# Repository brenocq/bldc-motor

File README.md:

<div align="center">
  
</div>

# BLDC Motor Controller

> [!NOTE]
> This project is currently in active development. Features and documentation are subject to change.

## Table of Contents
- [Project Overview](#project-overview)
- [Folder Structure](#folder-structure)
- [Mechanical](#mechanical)
- [Electronics](#electronics)
  - [MCU PCB (Top Board)](#mcu-pcb-top-board)
  - [Power PCB (Bottom Board)](#power-pcb-bottom-board)
- [Firmware](#firmware)
- [Simulation](#simulation)
- [Results](#results)
- [License](#license)

---

## Project Overview

This project aims to develop a **high-precision Brushless DC (BLDC) motor controller** from scratch, covering both hardware and firmware aspects. The controller is designed for advanced motor control applications, leveraging a powerful STM32 microcontroller, a dedicated motor driver IC, and comprehensive sensing capabilities for precise operation and rotor position estimation.

The core of the system is a custom two-board stack: an MCU board housing the main control logic and a power board managing motor drive and sensing.

## Folder Structure

The project is organized into logical directories to enhance maintainability and readability:

* `simulation/`: Contains code and files related to motor control simulation.
* `mechanical/`: Houses all mechanical design files (CAD models, part designs).
* `electronics/`: Stores KiCad project files for both the MCU and Power PCBs, including schematics and PCB layouts.
* `firmware/`: Contains all the embedded software for the STM32 microcontroller.
* `controller/`: Specific implementations of motor control algorithms (trapezoidal, FOC).
* `common/`: Shared utilities and communication definitions across different parts of the project.

---

## Mechanical

The mechanical aspects of this project are centered around integrating the custom electronics with an off-the-shelf **EM3215 BLDC motor**. It's important to note that, for this specific project, the **motor's original windings are being utilized**, and there are no plans to re-wrap the wire around the coils. The `mechanical` folder contains various CAD files (FreeCAD) for components like the rotor adapter, chassis, and PCB cutouts, ensuring a perfect fit and robust assembly.

<div align="center">
  
</div>

---

## Electronics

The electronics consist of two interconnected custom-designed Printed Circuit Boards (PCBs), designed using **KiCad**. Both boards are **4-layer designs** to facilitate efficient signal routing and power integrity. A **Molex PCB stack connector** is used to establish a robust electrical connection between the MCU and Power PCBs.

### MCU PCB (Top Board)

The top PCB serves as the brain of the controller, housing the main microcontroller and various sensors and interfaces for user interaction and precise feedback.

| Top Layer | Layer 1 | Layer 2 | Bottom Layer | 3D Top View | 3D Bottom View |
| :------------------: | :---------------: | :---------------: | :---------------------: | :---------: | :------------: |
|  |  |  |  |  |  |

**MCU PCB Key Components:**
- **STM32F4 Microcontroller:** The central processing unit for control algorithms, sensor data acquisition, and communication.
- **AS5048A Angle Position Encoder:** Provides 14-bit absolute rotor position feedback for precise commutation and control.
- **SK6805 LED Ring:** A customizable visual indicator for status and debugging.
- **Reset Button:** For convenient system resets.
- **ISM330DHCX IMU (Inertial Measurement Unit):** Provides acceleration and angular velocity data, useful for advanced motion control or system stabilization.

**MCU PCB v1.0 Release Package:**
- **[KiCad Project](https://github.com/brenocq/bldc-motor/tree/electronics/v1.0/electronics/BLDCM-MCU)**
- **[Schematic (PDF)](https://github.com/brenocq/bldc-motor/blob/electronics/v1.0/electronics/BLDCM-MCU/BLDCM-MCU.pdf)**
- **[Interactive BOM (HTML)](https://brenocq.s3.us-east-1.amazonaws.com/BLDCM/BLDCM-MCU-BOM-v1.0.html)**
- **[Gerbers (ZIP)](https://github.com/brenocq/bldc-motor/releases/download/electronics%2Fv1.0/BLDCM-MCU-v1.0-gerber.zip)**

### Power PCB (Bottom Board)

The bottom PCB handles the high-current motor driving functions and essential power monitoring.

| Top Layer | Layer 1 | Layer 2 | Bottom Layer | 3D Top View | 3D Bottom View |
| :------------------: | :---------------: | :---------------: | :---------------------: | :---------: | :------------: |
|  |  |  |  |  |  |

**Power PCB Key Components:**
- **TMC6300 Motor Driver:** A 3-phase motor driver that translates the MCU's PWM and control signals into high-current outputs for the motor phases.
- **TCAN1462 CAN Transceiver:** Enables robust CAN FD communication for daisy-chaining motors in series.
- **J-Link Connector:** Provides easy SWD debugging and programming for the STM32 microcontroller.
- **USB Connector:** Facilitates direct USB Full-Speed communication for data logging, control, and power input.
- **Micro-Lock Plus Connectors:** Robust 4-pin Molex connectors that provide a vibration-resistant link for power delivery and CAN bus communications.
- **Voltage Sensors (x4):** One monitors the DC bus voltage, while three dedicated sensors measure filtered phase voltages for safe operation and FOC.
- **INA240 Current Sensors (x3):** Three precision analog-output current sensors enable high-speed, accurate phase current measurement for FOC.

**Power PCB v1.0 Release Package:**
- **[KiCad Project](https://github.com/brenocq/bldc-motor/tree/electronics/v1.0/electronics/BLDCM-Power)**
- **[Schematic (PDF)](https://github.com/brenocq/bldc-motor/blob/electronics/v1.0/electronics/BLDCM-Power/BLDCM-Power.pdf)**
- **[Interactive BOM (HTML)](https://brenocq.s3.us-east-1.amazonaws.com/BLDCM/BLDCM-Power-BOM-v1.0.html)**
- **[Gerbers (ZIP)](https://github.com/brenocq/bldc-motor/releases/download/electronics%2Fv1.0/BLDCM-Power-v1.0-gerber.zip)**

---

## Firmware

The firmware, developed for the **STM32F4** microcontroller, is the intelligence behind the motor control. It includes:

* **Low-level Peripheral Drivers:** Custom drivers for ADC, timers, GPIO, SPI, I2C, UART, USB, and DMA to efficiently manage hardware resources.
* **Motor Control Algorithms:** Implementation of both **trapezoidal** and **Field-Oriented Control (FOC)** algorithms, located in the `controller` directory, to provide flexible and high-performance motor driving capabilities.
* **Sensor Integration:** Code to interface with the MT6701 encoder, INA239-Q1 current sensors, voltage sensor, and ISM330DHCX IMU for comprehensive feedback.
* **System Utilities:** Logging, error handling, and platform-specific configurations for the STM32 environment.

_The firmware architecture and design decisions will be documented in the future._

---

## Simulation

The `simulation` directory contains resources for simulating the BLDC motor system and visualizing the sensor data in real time. This allows for testing and validating control algorithms and system behavior in a virtual environment before deployment on the hardware. The `bldc.atta` file can be opened with [Atta](https://github.com/brenocq/atta), and it implements a basic motor model simulation and plotting of sensor data.

_Instructions on how to run the BLDCM simulation with [Atta](https://github.com/brenocq/atta) will be added in the future_

---

## Results

Below are some pictures/videos taken during the development. The controller design and calibration procedures will be explained in depth in the future :)

https://github.com/user-attachments/assets/e86b0316-7ecf-4e15-9d3b-c0315d690438

<div align="center">

</div>

## License
This project is licensed under the MIT License - check [LICENSE](LICENSE) for details.

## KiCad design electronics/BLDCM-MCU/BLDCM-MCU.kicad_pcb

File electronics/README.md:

# BLDCM Electronics
These KiCad projects were made with KiCad 9.0, make sure to use the same version or a newer one.

The schematic PDFs are available in `BLDCM-Power/BLDCM-Power.pdf` and `BLDCM-MCU/BLDCM-MCU.pdf`. The Gerber files and interactive BOM can be found in the release section of the repository.

> [!IMPORTANT]
> This project depends on the [BrenoCQ KiCad library](https://github.com/brenocq/brenocq-kicad-library), included as a Git submodule. To ensure all symbols, footprints, and 3D models are available, you must initialize the submodules:
>
> ```bash
> git submodule update --init --recursive
> ```

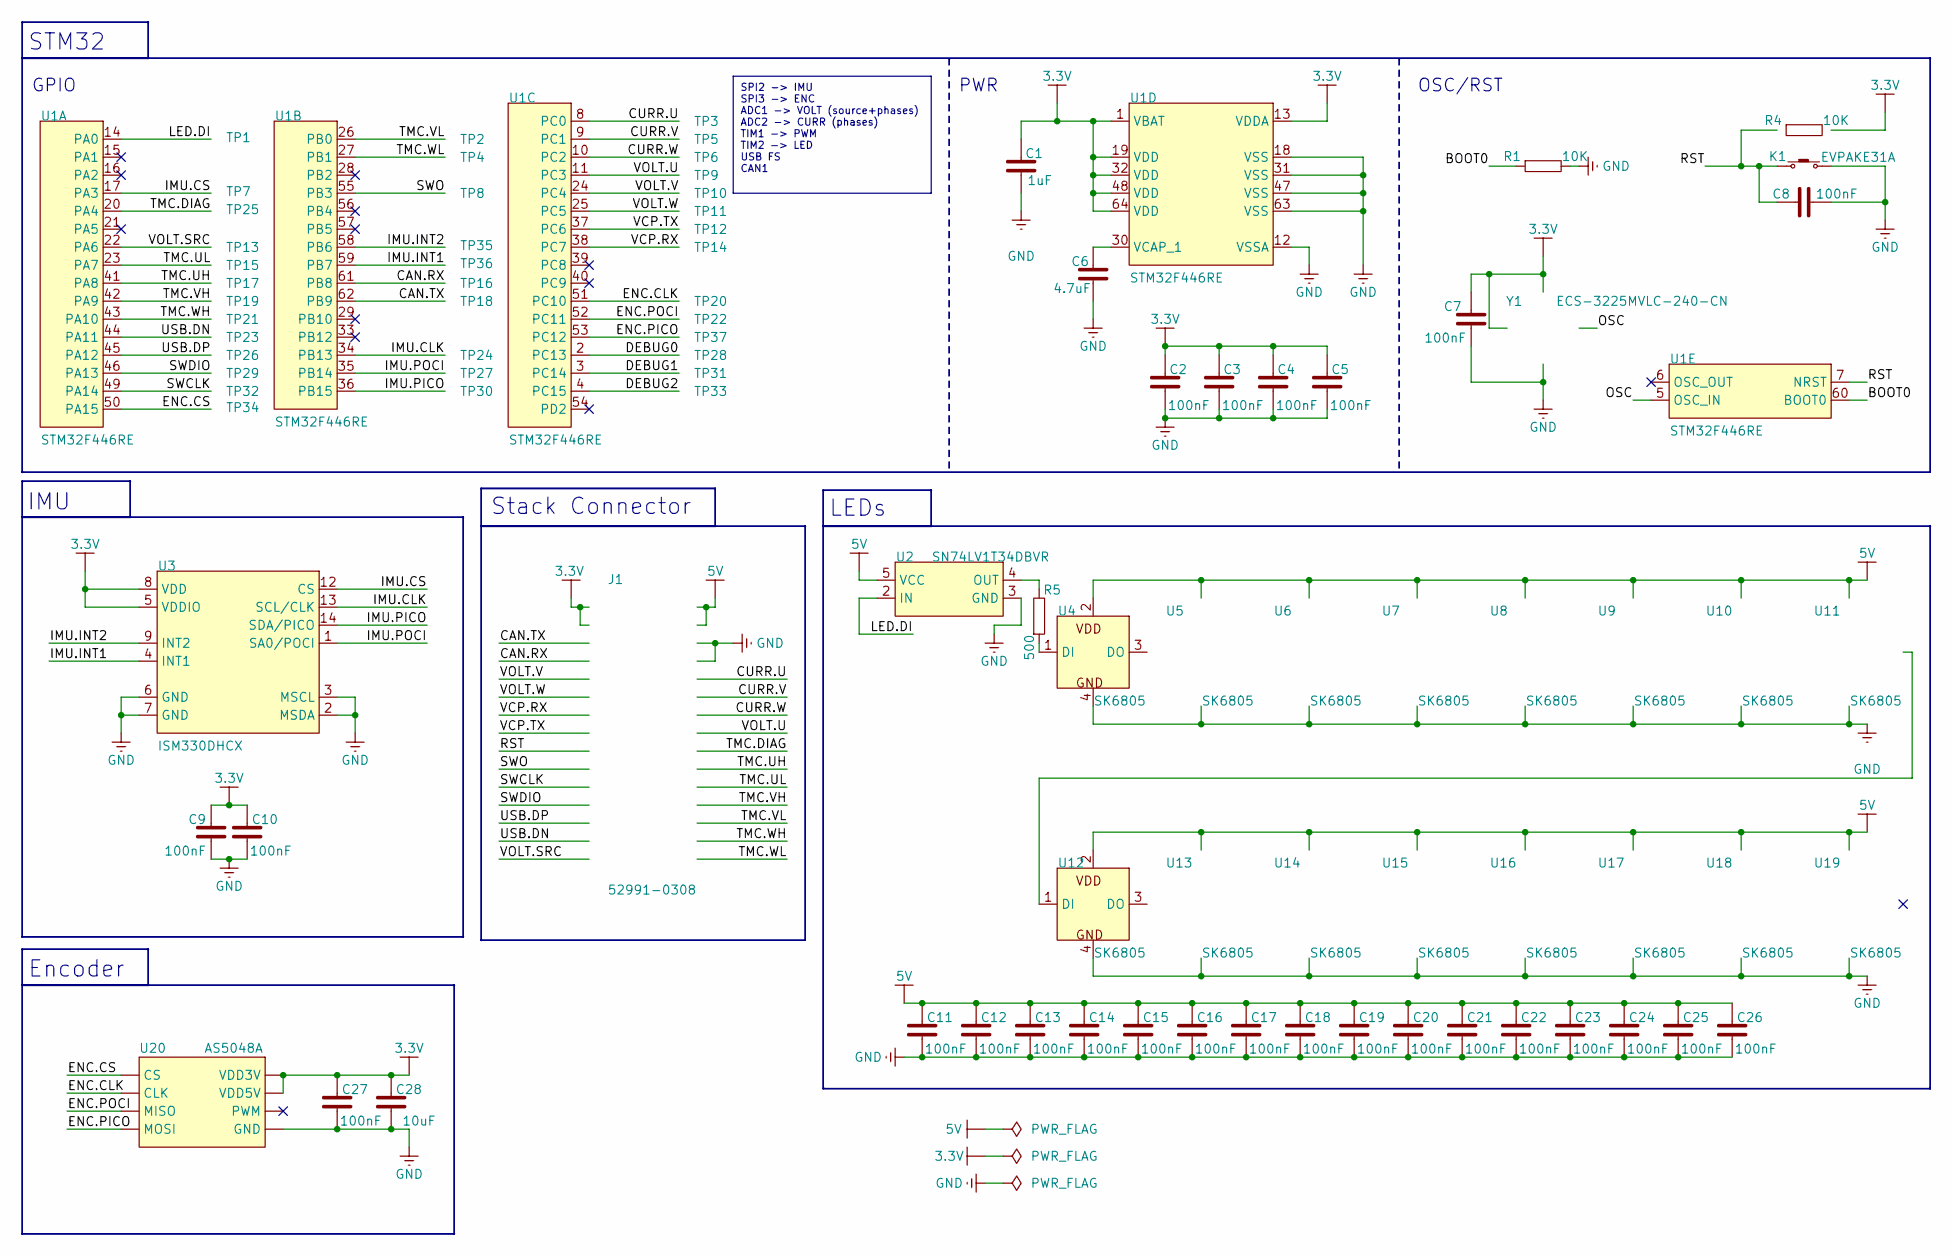
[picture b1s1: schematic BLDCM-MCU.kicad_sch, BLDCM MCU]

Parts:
C1: 1uF; C_0402
C2, C3, C4, C5, C7, C8, C9, C10, C11, C12, C13, C14, C15, C16, C17, C18, C19, C20, C21, C22, C23, C24, C25, C26, C27: 100nF; C_0402
C6: 4.7uF; C_0603
C28: 10uF; C_0805
J1: 52991-0308
K1: EVPAKE31A
R1, R4: 10K; R_0402
R5: 500; R_0402
TP1, TP2, TP3, TP4, TP5, TP6, TP7, TP8, TP9, TP10, TP11, TP12, TP13, TP14, TP15, TP16, TP17, TP18, TP19, TP20, TP21, TP22, TP23, TP24, TP25, TP26, TP27, TP28, TP29, TP30, TP31, TP32, TP33, TP34, TP35, TP36, TP37: Test point 0.5mm; TP_0.5mm
U1: STM32F446RE; LQFP64
U2: SN74LV1T34DBVR; SOT-23-5
U3: ISM330DHCX; LGA-14L
U4, U5, U6, U7, U8, U9, U10, U11, U12, U13, U14, U15, U16, U17, U18, U19: SK6805; LED-1515
U20: AS5048A; TSSOP-14
Y1: ECS-3225MVLC-240-CN; Crystal_3225

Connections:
3.3V: C1.2, C2.2, C3.2, C4.2, C5.2, C7.2, C9.2, C10.2, C27.2, C28.2, J1.1, J1.3, R4.2, U1.1 (VBAT), U1.13 (VDDA), U1.19 (VDD), U1.32 (VDD), U1.48 (VDD), U1.64 (VDD), U3.5 (VDDIO), U3.8 (VDD), U20.11 (VDD5V), U20.12 (VDD3V), Y1.1, Y1.4
5V: C11.2, C12.2, C13.2, C14.2, C15.2, C16.2, C17.2, C18.2, C19.2, C20.2, C21.2, C22.2, C23.2, C24.2, C25.2, C26.2, J1.2, J1.4, U2.5 (VCC), U4.2 (VDD), U5.2 (VDD), U6.2 (VDD), U7.2 (VDD), U8.2 (VDD), U9.2 (VDD), U10.2 (VDD), U11.2 (VDD), U12.2 (VDD), U13.2 (VDD), U14.2 (VDD), U15.2 (VDD), U16.2 (VDD), U17.2 (VDD), U18.2 (VDD), U19.2 (VDD)
/BOOT0: R1.1, U1.60 (BOOT0)
/CAN.RX: J1.7, TP16.1, U1.61 (PB8)
/CAN.TX: J1.5, TP18.1, U1.62 (PB9)
/CURR.U: J1.10, TP3.1, U1.8 (PC0)
/CURR.V: J1.12, TP5.1, U1.9 (PC1)
/CURR.W: J1.14, TP6.1, U1.10 (PC2)
/DEBUG0: TP28.1, U1.2 (PC13)
/DEBUG1: TP31.1, U1.3 (PC14)
/DEBUG2: TP33.1, U1.4 (PC15)
/ENC.CLK: TP20.1, U1.51 (PC10), U20.2 (CLK)
/ENC.CS: TP34.1, U1.50 (PA15), U20.1 (CS)
/ENC.PICO: TP37.1, U1.53 (PC12), U20.4 (MOSI)
/ENC.POCI: TP22.1, U1.52 (PC11), U20.3 (MISO)
/IMU.CLK: TP24.1, U1.34 (PB13), U3.13 (SCL/CLK)
/IMU.CS: TP7.1, U1.17 (PA3), U3.12 (CS)
/IMU.INT1: TP36.1, U1.59 (PB7), U3.4 (INT1)
/IMU.INT2: TP35.1, U1.58 (PB6), U3.9 (INT2)
/IMU.PICO: TP30.1, U1.36 (PB15), U3.14 (SDA/PICO)
/IMU.POCI: TP27.1, U1.35 (PB14), U3.1 (SA0/POCI)
/LED.DI: TP1.1, U1.14 (PA0), U2.2 (IN)
/OSC: U1.5 (OSC_IN), Y1.3
/RST: C8.2, J1.17, K1.1, R4.1, U1.7 (NRST)
/SWCLK: J1.21, TP32.1, U1.49 (PA14)
/SWDIO: J1.23, TP29.1, U1.46 (PA13)
/SWO: J1.19, TP8.1, U1.55 (PB3)
/TMC.DIAG: J1.18, TP25.1, U1.20 (PA4)
/TMC.UH: J1.20, TP17.1, U1.41 (PA8)
/TMC.UL: J1.22, TP15.1, U1.23 (PA7)
/TMC.VH: J1.24, TP19.1, U1.42 (PA9)
/TMC.VL: J1.26, TP2.1, U1.26 (PB0)
/TMC.WH: J1.28, TP21.1, U1.43 (PA10)
/TMC.WL: J1.30, TP4.1, U1.27 (PB1)
/USB.DN: J1.27, TP23.1, U1.44 (PA11)
/USB.DP: J1.25, TP26.1, U1.45 (PA12)
/VCP.RX: J1.13, TP14.1, U1.38 (PC7)
/VCP.TX: J1.15, TP12.1, U1.37 (PC6)
/VOLT.SRC: J1.29, TP13.1, U1.22 (PA6)
/VOLT.U: J1.16, TP9.1, U1.11 (PC3)
/VOLT.V: J1.9, TP10.1, U1.24 (PC4)
/VOLT.W: J1.11, TP11.1, U1.25 (PC5)
GND: C1.1, C2.1, C3.1, C4.1, C5.1, C6.1, C7.1, C8.1, C9.1, C10.1, C11.1, C12.1, C13.1, C14.1, C15.1, C16.1, C17.1, C18.1, C19.1, C20.1, C21.1, C22.1, C23.1, C24.1, C25.1, C26.1, C27.1, C28.1, J1.6, J1.8, K1.2, R1.2, U1.12 (VSSA), U1.18 (VSS), U1.31 (VSS), U1.47 (VSS), U1.63 (VSS), U2.3 (GND), U3.2 (MSDA), U3.3 (MSCL), U3.6 (GND), U3.7 (GND), U4.4 (GND), U5.4 (GND), U6.4 (GND), U7.4 (GND), U8.4 (GND), U9.4 (GND), U10.4 (GND), U11.4 (GND), U12.4 (GND), U13.4 (GND), U14.4 (GND), U15.4 (GND), U16.4 (GND), U17.4 (GND), U18.4 (GND), U19.4 (GND), U20.13 (GND), Y1.2
unnamed: C6.2, U1.30 (VCAP_1)
unnamed: R5.2, U2.4 (OUT)
unnamed: R5.1, U4.1 (DI)
unnamed: U4.3 (DO), U5.1 (DI)
unnamed: U5.3 (DO), U6.1 (DI)
unnamed: U6.3 (DO), U7.1 (DI)
unnamed: U7.3 (DO), U8.1 (DI)
unnamed: U8.3 (DO), U9.1 (DI)
unnamed: U9.3 (DO), U10.1 (DI)
unnamed: U10.3 (DO), U11.1 (DI)
unnamed: U11.3 (DO), U12.1 (DI)
unnamed: U12.3 (DO), U13.1 (DI)
unnamed: U13.3 (DO), U14.1 (DI)
unnamed: U14.3 (DO), U15.1 (DI)
unnamed: U15.3 (DO), U16.1 (DI)
unnamed: U16.3 (DO), U17.1 (DI)
unnamed: U17.3 (DO), U18.1 (DI)
unnamed: U18.3 (DO), U19.1 (DI)

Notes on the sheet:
STM32
IMU
LEDs
Stack Connector
Encoder
OSC/RST
GPIO
PWR
SPI2 -> IMU SPI3 -> ENC ADC1 -> VOLT (source+phases) ADC2 -> CURR (phases) TIM1 -> PWM TIM2 -> LED USB FS CAN1

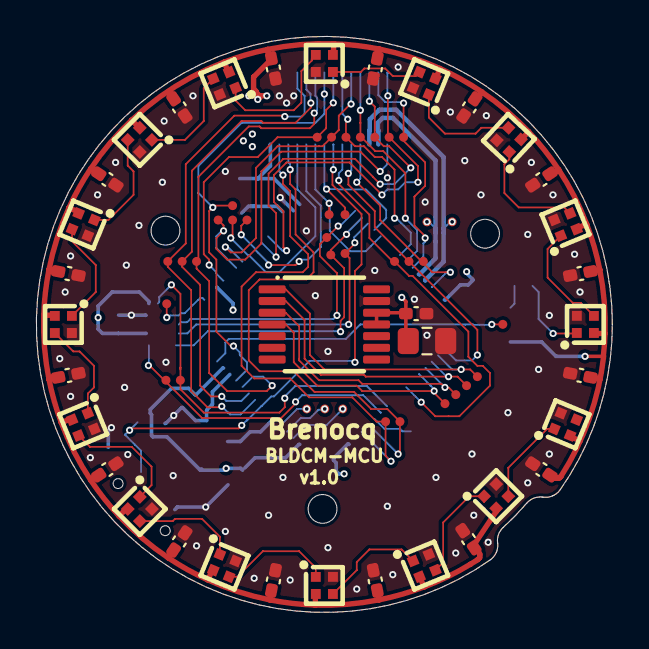
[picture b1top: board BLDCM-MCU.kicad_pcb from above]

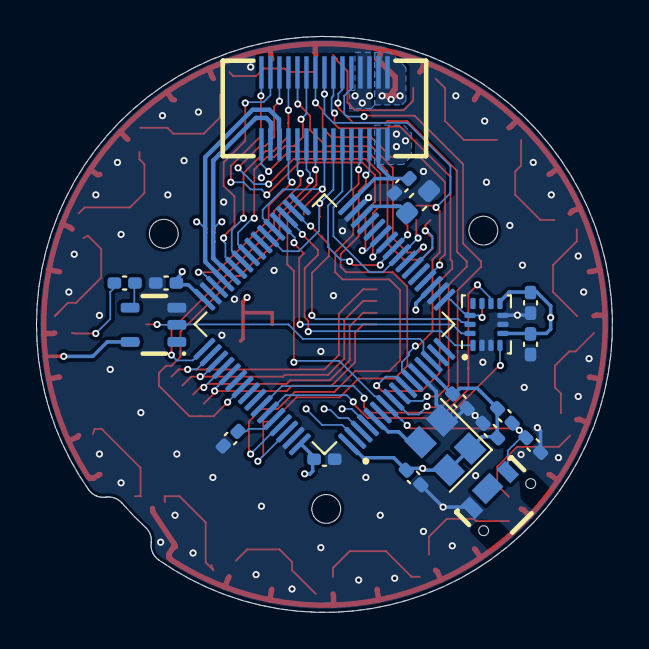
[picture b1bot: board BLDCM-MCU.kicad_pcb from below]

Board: 4 copper layers, 32.0 x 32.0 mm, 91 parts (19 on the bottom side), 61 nets.

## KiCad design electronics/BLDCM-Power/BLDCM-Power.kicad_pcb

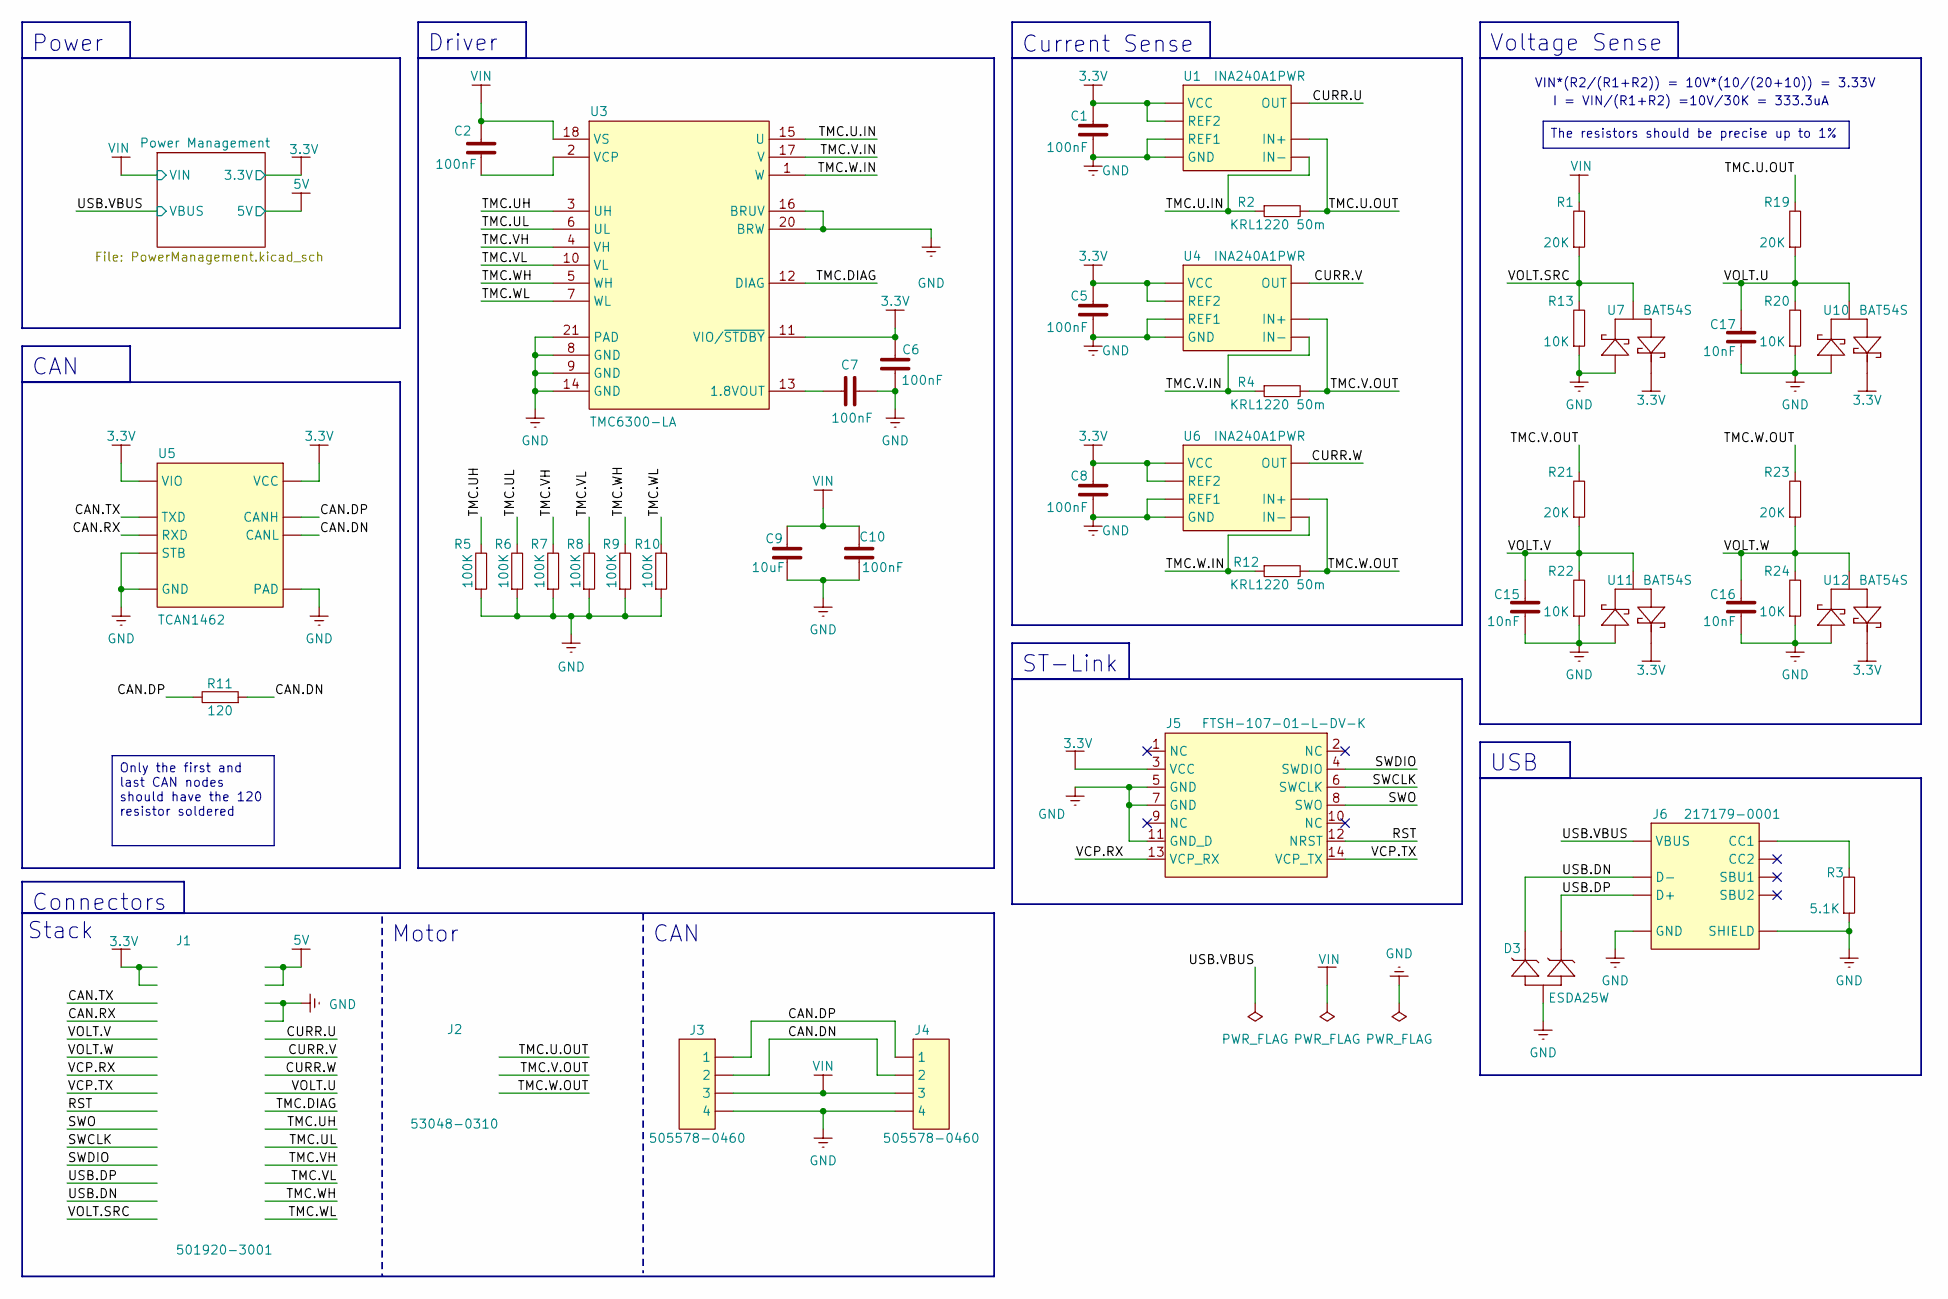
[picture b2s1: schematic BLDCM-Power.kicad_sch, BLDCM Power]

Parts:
C1, C2, C5, C6, C7, C8, C10: 100nF; C_0402
C9: 10uF; C_0805
C15, C16, C17: 10nF; C_0402
D3: ESDA25W; SOT-323
J1: 501920-3001
J2: 53048-0310
J3, J4: 505578-0460
J5: FTSH-107-01-L-DV-K; FTSH-107-01-L-DV-K-TR
J6: 217179-0001
R1, R19, R21, R23: 20K; R_0402
R2, R4, R12: KRL1220 50m; KRL1220
R3: 5.1K; R_0402
R5, R6, R7, R8, R9, R10: 100K; R_0402
R11: 120; R_0402
R13, R20, R22, R24: 10K; R_0402
U1, U4, U6: INA240A1PWR; TSSOP-8
U3: TMC6300-LA; QFN-20
U5: TCAN1462; VSON-8
U7, U10, U11, U12: BAT54S; SOT-23

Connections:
3.3V: C1.1, C5.1, C6.2, C8.1, J1.1, J1.3, J5.3 (VCC), U1.5 (VCC), U1.6 (REF2), U3.11 (VIO/~STDBY), U4.5 (VCC), U4.6 (REF2), U5.3 (VCC), U5.5 (VIO), U6.5 (VCC), U6.6 (REF2), U7.2, U10.2, U11.2, U12.2; also elsewhere on the board
5V: J1.2, J1.4; also elsewhere on the board
/CAN.DN: J3.2, J4.2, R11.1, U5.6 (CANL)
/CAN.DP: J3.1, J4.1, R11.2, U5.7 (CANH)
/CAN.RX: J1.7, U5.4 (RXD)
/CAN.TX: J1.5, U5.1 (TXD)
/CURR.U: J1.10, U1.8 (OUT)
/CURR.V: J1.12, U4.8 (OUT)
/CURR.W: J1.14, U6.8 (OUT)
/RST: J1.17, J5.12 (NRST)
/SWCLK: J1.21, J5.6 (SWCLK)
/SWDIO: J1.23, J5.4 (SWDIO)
/SWO: J1.19, J5.8 (SWO)
/TMC.DIAG: J1.18, U3.12 (DIAG)
/TMC.U.IN: R2.1, U1.3 (IN-), U3.15 (U)
/TMC.U.OUT: J2.1, R2.2, R19.2, U1.2 (IN+)
/TMC.UH: J1.20, R5.2, U3.3 (UH)
/TMC.UL: J1.22, R6.2, U3.6 (UL)
/TMC.V.IN: R4.1, U3.17 (V), U4.3 (IN-)
/TMC.V.OUT: J2.2, R4.2, R21.2, U4.2 (IN+)
/TMC.VH: J1.24, R7.2, U3.4 (VH)
/TMC.VL: J1.26, R8.2, U3.10 (VL)
/TMC.W.IN: R12.1, U3.1 (W), U6.3 (IN-)
/TMC.W.OUT: J2.3, R12.2, R23.2, U6.2 (IN+)
/TMC.WH: J1.28, R9.2, U3.5 (WH)
/TMC.WL: J1.30, R10.2, U3.7 (WL)
/USB.DN: D3.1, J1.27, J6.A7 (D-), J6.B7 (D-2)
/USB.DP: D3.2, J1.25, J6.A6 (D+), J6.B6 (D+2)
/VCP.RX: J1.13, J5.13 (VCP_RX)
/VCP.TX: J1.15, J5.14 (VCP_TX)
/VOLT.SRC: J1.29, R1.1, R13.2, U7.3
/VOLT.U: C17.2, J1.16, R19.1, R20.2, U10.3
/VOLT.V: C15.2, J1.9, R21.1, R22.2, U11.3
/VOLT.W: C16.2, J1.11, R23.1, R24.2, U12.3
GND: C1.2, C5.2, C6.1, C7.1, C8.2, C9.1, C10.1, C15.1, C16.1, C17.1, D3.3, J1.6, J1.8, J3.4, J4.4, J5.5 (GND), J5.7 (GND), J5.11 (GND_D), J6.A1_B12 (GND), J6.B1_A12 (GND), J6.SH1 (SHIELD), J6.SH2 (SHIELD), J6.SH3 (SHIELD), J6.SH4 (SHIELD), R3.1, R5.1, R6.1, R7.1, R8.1, R9.1, R10.1, R13.1, R20.1, R22.1, R24.1, U1.4 (GND), U1.7 (REF1), U3.8 (GND), U3.9 (GND), U3.14 (GND), U3.16 (BRUV), U3.20 (BRW), U3.21 (PAD), U4.4 (GND), U4.7 (REF1), U5.2 (GND), U5.8 (STB), U5.PAD, U6.4 (GND), U6.7 (REF1), U7.1, U10.1, U11.1, U12.1; also elsewhere on the board
unnamed: J6.A5 (CC1), R3.2
unnamed: C7.2, U3.13 (1.8VOUT)
unnamed: C2.1, U3.2 (VCP)
VBUS: J6.A4_B9 (VBUS), J6.B4_A9 (VBUS); also elsewhere on the board
VIN: C2.2, C9.2, C10.2, J3.3, J4.3, R1.2, U3.18 (VS); also elsewhere on the board

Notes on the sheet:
ST-Link
I = VIN/(R1+R2) =10V/30K = 333.3uA
Driver
Stack
Power
CAN
VIN*(R2/(R1+R2)) = 10V*(10/(20+10)) = 3.33V
Motor
Voltage Sense
USB
Connectors
Current Sense
The resistors should be precise up to 1%
Only the first and last CAN nodes should have the 120 resistor soldered

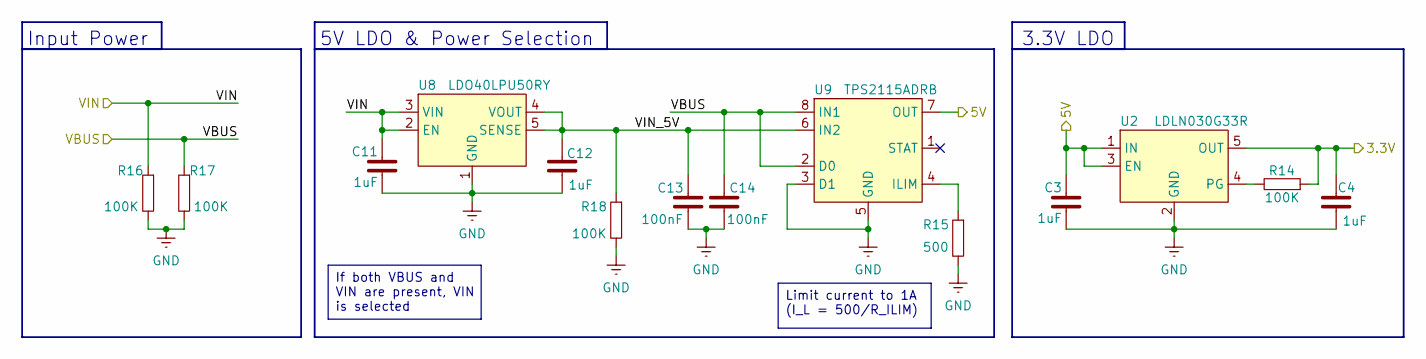
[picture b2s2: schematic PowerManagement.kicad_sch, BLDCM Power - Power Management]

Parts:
C3, C4, C11, C12: 1uF; C_0402
C13, C14: 100nF; C_0402
R14, R16, R17, R18: 100K; R_0402
R15: 500; R_0402
U2: LDLN030G33R; TSOT-23-5
U8: LDO40LPU50RY; DFN-6-3x3
U9: TPS2115ADRB; VSON-8

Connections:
3.3V: C4.2, R14.1, U2.5 (OUT); also elsewhere on the board
5V: C3.2, U2.1 (IN), U2.3 (EN), U9.7 (OUT); also elsewhere on the board
/Power Management/VIN_5V: C12.2, C13.1, R18.1, U8.4 (VOUT), U8.5 (SENSE), U9.6 (IN2)
GND: C3.1, C4.1, C11.1, C12.1, C13.2, C14.2, R15.2, R16.2, R17.2, R18.2, U2.2 (GND), U8.1 (GND), U8.PAD, U9.3 (D1), U9.5 (GND), U9.PAD; also elsewhere on the board
unnamed: R14.2, U2.4 (PG)
unnamed: R15.1, U9.4 (ILIM)
VBUS: C14.1, R17.1, U9.2 (D0), U9.8 (IN1); also elsewhere on the board
VIN: C11.2, R16.1, U8.2 (EN), U8.3 (VIN); also elsewhere on the board

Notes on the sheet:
Input Power
3.3V LDO
5V LDO & Power Selection
Limit current to 1A (I_L = 500/R_ILIM)
If both VBUS and VIN are present, VIN is selected

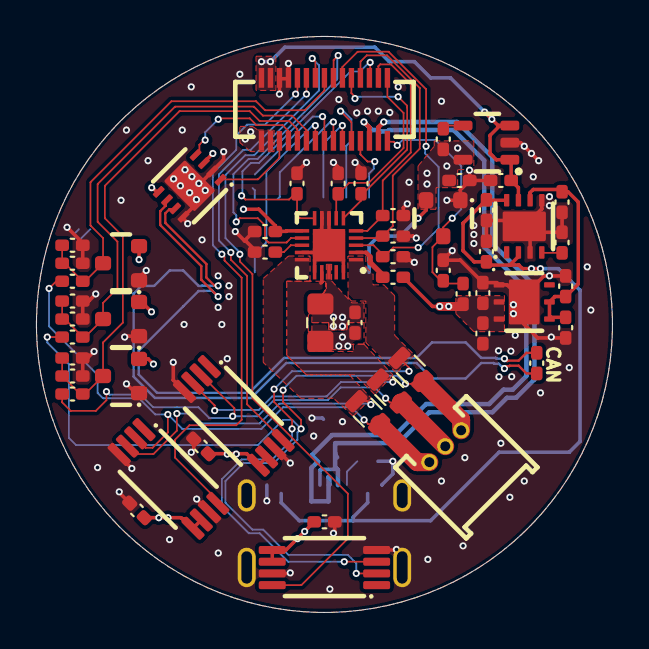
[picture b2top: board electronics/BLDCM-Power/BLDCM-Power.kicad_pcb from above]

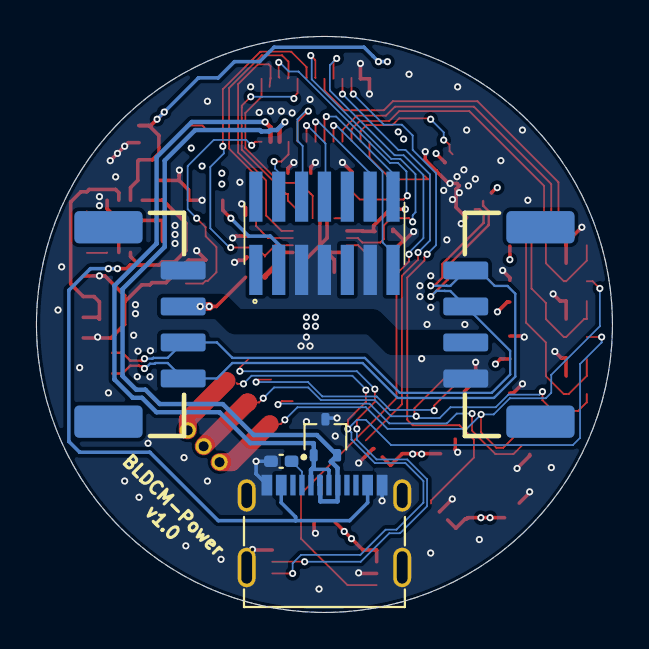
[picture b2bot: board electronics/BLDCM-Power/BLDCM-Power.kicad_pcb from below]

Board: 4 copper layers, 32.0 x 32.0 mm, 60 parts (6 on the bottom side), 43 nets.

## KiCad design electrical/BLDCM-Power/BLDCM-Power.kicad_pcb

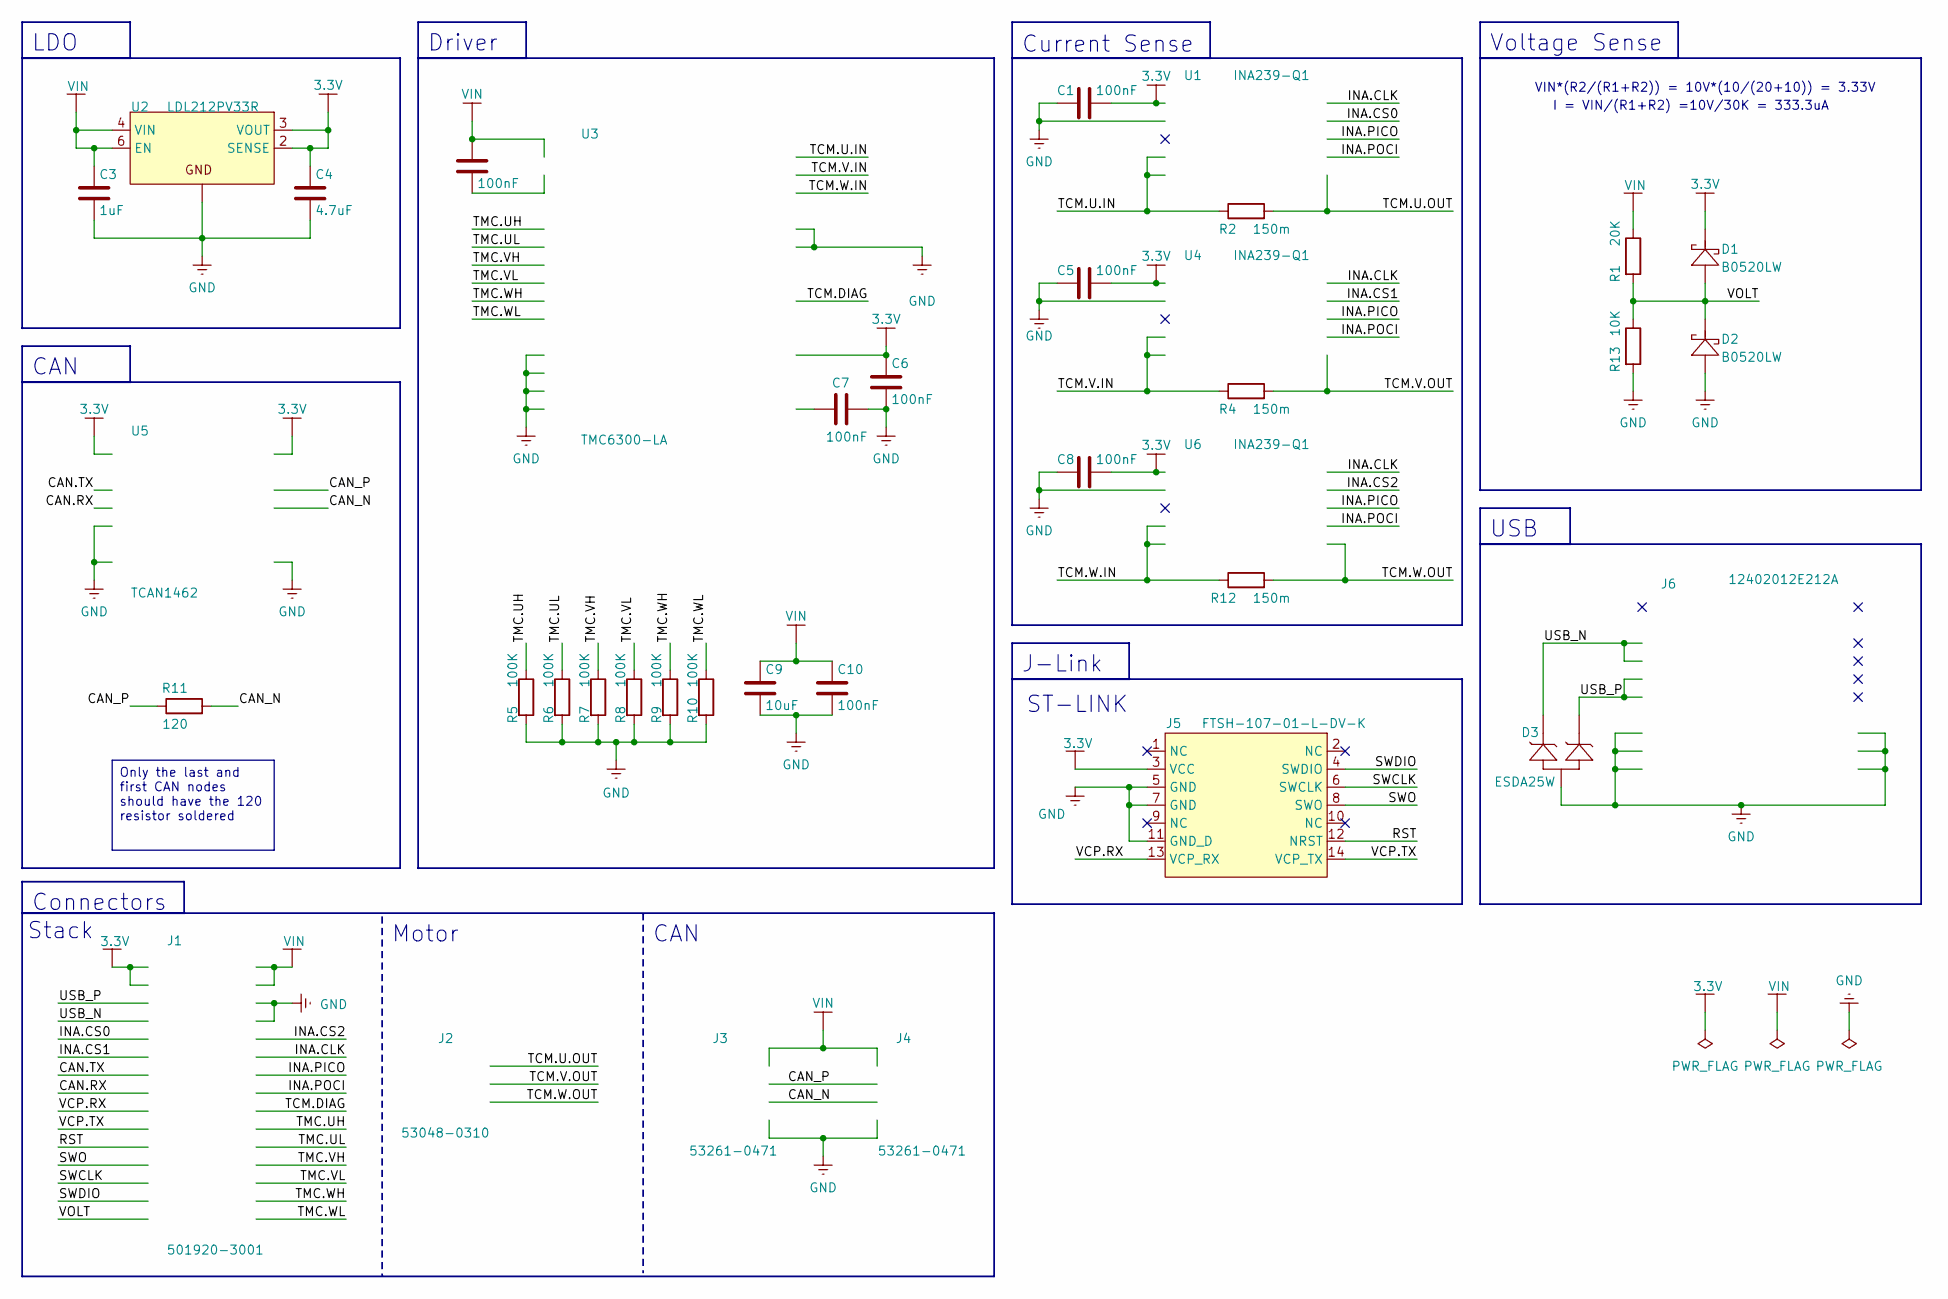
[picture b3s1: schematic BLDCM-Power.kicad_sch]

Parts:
C1, C2, C5, C6, C7, C8, C10: 100nF; C_0402
C3: 1uF; C_0603
C4: 4.7uF; C_0603
C9: 10uF; C_0805
D1, D2: B0520LW; SOD-123
D3: ESDA25W; SOT-323
J1: 501920-3001
J2: 53048-0310
J3, J4: 53261-0471
J5: FTSH-107-01-L-DV-K; FTSH-107-01-L-DV-K-TR
J6: 12402012E212A
R1: 20K; R_0402
R2, R4, R12: 150m; R_1210
R5, R6, R7, R8, R9, R10: 100K; R_0402
R11: 120; R_0402
R13: 10K; R_0402
U1, U4, U6: INA239-Q1; VSSOP-10
U2: LDL212PV33R; DFN-6-2x2
U3: TMC6300-LA; QFN-20
U5: TCAN1462; VSON-8

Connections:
3.3V: C1.2, C4.1, C5.2, C6.1, C8.2, D1.2, J1.1, J1.3, J5.3 (VCC), U1.6 (VCC), U2.2 (SENSE), U2.3 (VOUT), U3.11 (VIO/~STDBY), U4.6 (VCC), U5.3 (VCC), U5.5 (VIO), U6.6 (VCC)
/CAN.RX: J1.15, U5.4 (RXD)
/CAN.TX: J1.13, U5.1 (TXD)
/CAN_N: J3.3, J4.3, R11.2, U5.6 (CANL)
/CAN_P: J3.2, J4.2, R11.1, U5.7 (CANH)
/INA.CLK: J1.12, U1.5 (CLK), U4.5 (CLK), U6.5 (CLK)
/INA.CS0: J1.9, U1.1 (CS)
/INA.CS1: J1.11, U4.1 (CS)
/INA.CS2: J1.10, U6.1 (CS)
/INA.PICO: J1.14, U1.2 (PICO), U4.2 (PICO), U6.2 (PICO)
/INA.POCI: J1.16, U1.4 (POCI), U4.4 (POCI), U6.4 (POCI)
/RST: J1.21, J5.12 (NRST)
/SWCLK: J1.25, J5.6 (SWCLK)
/SWDIO: J1.27, J5.4 (SWDIO)
/SWO: J1.23, J5.8 (SWO)
/TCM.DIAG: J1.18, U3.12 (DIAG)
/TCM.U.IN: R2.1, U1.8 (VBUS), U1.10 (IN+), U3.15 (U)
/TCM.U.OUT: J2.1, R2.2, U1.9 (IN-)
/TCM.V.IN: R4.1, U3.17 (V), U4.8 (VBUS), U4.10 (IN+)
/TCM.V.OUT: J2.2, R4.2, U4.9 (IN-)
/TCM.W.IN: R12.1, U3.1 (W), U6.8 (VBUS), U6.10 (IN+)
/TCM.W.OUT: J2.3, R12.2, U6.9 (IN-)
/TMC.UH: J1.20, R5.1, U3.3 (UH)
/TMC.UL: J1.22, R6.1, U3.6 (UL)
/TMC.VH: J1.24, R7.1, U3.4 (VH)
/TMC.VL: J1.26, R8.1, U3.10 (VL)
/TMC.WH: J1.28, R9.1, U3.5 (WH)
/TMC.WL: J1.30, R10.1, U3.7 (WL)
/USB_N: D3.1, J1.7, J6.A7 (D-1), J6.B7 (D-2)
/USB_P: D3.2, J1.5, J6.A6 (D+1), J6.B6 (D+2)
/VCP.RX: J1.17, J5.13 (VCP_RX)
/VCP.TX: J1.19, J5.14 (VCP_TX)
/VOLT: D1.1, D2.2, J1.29, R1.2, R13.1
GND: C1.1, C3.2, C4.2, C5.1, C6.2, C7.2, C8.1, C9.2, C10.2, D2.1, D3.3, J1.6, J1.8, J3.4, J4.4, J5.5 (GND), J5.7 (GND), J5.11 (GND_D), J6.A1_B12 (GND), J6.B1_A12 (GND), J6.SH1 (SHIELD), J6.SH2 (SHIELD), J6.SH3 (SHIELD), J6.SH4 (SHIELD), R5.2, R6.2, R7.2, R8.2, R9.2, R10.2, R13.2, U1.7 (GND), U2.1 (GND), U2.PAD (GND), U3.8 (GND), U3.9 (GND), U3.14 (GND), U3.16 (BRUV), U3.20 (BRW), U3.21 (PAD), U4.7 (GND), U5.2 (GND), U5.8 (STB), U5.PAD, U6.7 (GND); also elsewhere on the board
unnamed: C7.1, U3.13 (1.8VOUT)
unnamed: C2.2, U3.2 (VCP)
VIN: C2.1, C3.1, C9.1, C10.1, J1.2, J1.4, J3.1, J4.1, R1.1, U2.4 (VIN), U2.6 (EN), U3.18 (VS)

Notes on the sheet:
J-Link
I = VIN/(R1+R2) =10V/30K = 333.3uA
Driver
Stack
CAN
ST-LINK
VIN*(R2/(R1+R2)) = 10V*(10/(20+10)) = 3.33V
Motor
Voltage Sense
USB
Connectors
Current Sense
LDO
Only the last and first CAN nodes should have the 120 resistor soldered

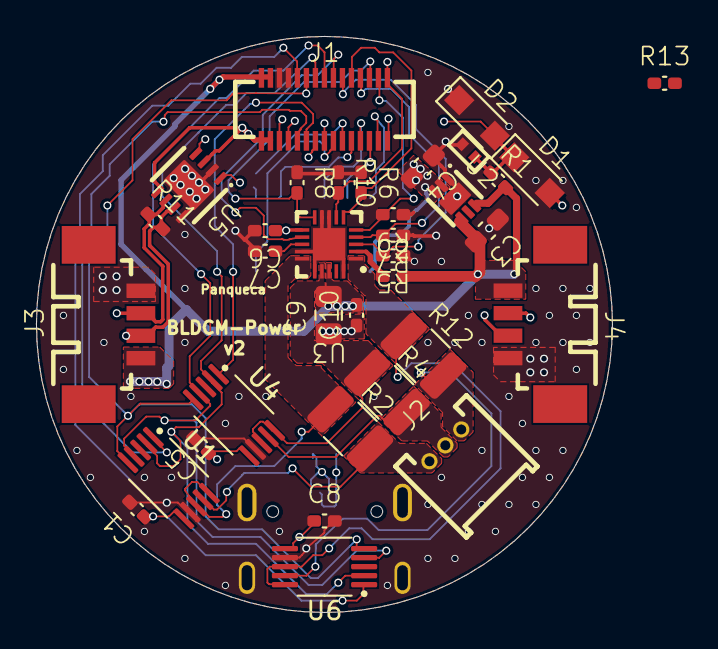
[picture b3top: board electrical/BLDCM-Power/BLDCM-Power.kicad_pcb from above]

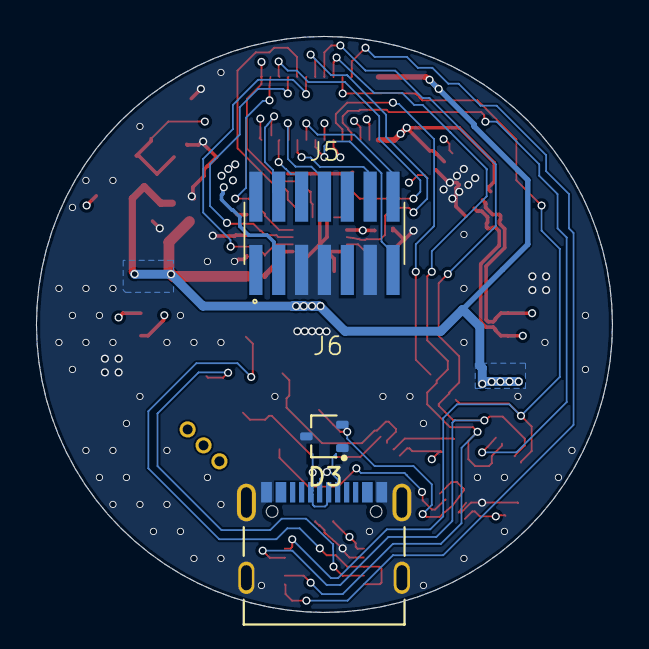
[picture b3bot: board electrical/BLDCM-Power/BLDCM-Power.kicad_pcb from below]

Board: 4 copper layers, 32.0 x 32.0 mm, 38 parts (3 on the bottom side), 37 nets.

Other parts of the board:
R3: 10K; RES_0402

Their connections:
GND: R3.1; also elsewhere on the board

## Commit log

2023-09-07 Feat: STM32 HAL
2023-09-07 Feat: Clock driver
2023-09-07 Feat: Starting GPIO driver
2023-09-08 Feat: Starting USB driver
2023-09-08 Feat: GDB working
2023-09-12 Feat: UART driver
2023-09-13 Feat: Encoder working
2023-09-14 Feat: Encoder CRC check
2023-09-15 Feat: ADC driver
2023-09-15 Feat: Voltage driver
2023-09-18 Feat: Motor driver
2023-09-19 Feat: Current driver
2023-09-21 Test: Motor driver rotation
2023-09-21 Feat: Logging
2023-09-21 Chore: Migrate from make to cmake
2023-09-23 Feat: Starting atta connector
2023-09-27 Feat: Starting BLDC simulation
2023-09-27 Feat: State space model setup
2023-09-28 Feat: State space model working
2023-09-28 Feat: Show motor orientation in 3D
2023-10-01 Feat: Atta connector CRC
2023-10-02 Feat: Atta connector COBS encode
2023-10-02 Feat: Starting trapezoidal commutation controller
2023-10-03 Feat: Atta connector tx packet handling
2023-10-03 Feat: Atta connector TX working
2023-10-03 Feat: Atta connector packet decoding
2023-10-03 Feat: Atta connector dynamic size support
2023-10-05 Feat: Atta connector receive packets
2023-10-05 Fix: Atta connector not all packets received
2023-10-07 Fix: Atta connector ACK/NACK
2023-10-07 Feat: Simulation using controller
2023-10-08 Feat: Atta connector STM32-Desktop working
2023-10-08 Feat: Plot sensors
2023-10-25 Refactor: Update motor model voltage
2023-10-25 Feat: FOC space vector PWM
2023-11-20 Fix: Compiling with freestanding
2023-11-21 Refactor: Prototype v1 GPIOs
2023-11-23 Fix: Clock with 24MHz crystal
2023-11-23 Feat: Logging with ITM
2023-11-23 Fix: USART6 not working
2023-11-23 Fix: Atta connector with STLINK
2023-11-24 Feat: Voltage driver working
2023-11-24 Feat: Starting led driver
2023-11-25 Feat: I2c driver
2023-11-25 Feat: Phase driver
2023-11-25 Feat: SPI driver
2023-11-26 Feat: Starting IMU driver
2023-11-30 Feat: Add trace option
2023-11-30 Fix: Wrong SPI initialization
2023-11-30 Feat: Read IMU data
2023-12-01 Feat: Starting timer driver
2023-12-01 Refactor: Remove logging macros
2023-12-01 Feat: Starting DMA driver
2023-12-01 Feat: Timer-DMA link
2023-12-01 Feat: Interrupt driver
2023-12-01 Feat: Starting DMA-PWM test
2023-12-03 Test: Encoder and motor driver
2023-12-06 Feat: Led driver working
2023-12-07 Refactor: Atta connector without ACK
2023-12-08 Refactor: Motor state streaming
2024-02-28 Refactor: FOC controller interface
2024-02-28 Refactor: Gpio pinout v2
2024-02-29 Refactor: Starting INA239 migration
2024-03-03 Refactor: Finish INA239 migration
2024-03-03 Feat: SPI peripheral configuration
2024-03-03 Feat: Plot IMU data
2024-03-03 Feat: Encoder with SPI
2024-03-03 Feat: LED rainbow
2024-03-06 Refactor: Reduce LED brightness
2024-03-06 Refactor: USB 48MHz clock
2024-03-06 Feat: USB init
2024-03-07 Feat: USB interrupts
2024-03-07 Feat: Starting USB descriptor
2024-03-11 Feat: USB set address
2024-03-12 Test: USB HID descriptors
2024-03-24 Motor timer configuration
2024-03-24 SVPWM working
2024-03-26 Plot clarke/park transform
2024-03-27 Starting encoder calibration
2024-04-02 Feat: UART DMA receive
2024-04-02 Feat: Starting UART DMA transmit
2025-04-09 Feat: Setup FreeCAD folder
2025-04-09 Feat: Setup KiCad project
2025-05-06 Feat: KiCad BLDCM-MCU schematic
2025-05-06 Feat: KiCad BLDCM-Power schematic
2025-05-06 Fix: BLDCM-Power ERC errors
2025-05-06 Fix: BLDCM-MCU ERC errors
2025-05-06 Fix: PCB resistor rotation
2025-05-06 Chore: Rename electrical to electronics
2025-05-06 Docs: KiCad installation instructions
2025-05-12 Feat: Finish MCU PCB routing
2025-05-12 Feat: Initial FreeCAD files
2025-05-12 Refactor: Power PCB resistor
2025-05-12 Chore: Configure Git LFS
2025-05-30 Feat: MCU schematic add VIN note
2025-05-30 Feat: Power PCB replace symbols with brenocq lib symbols
2025-05-31 Refactor(mechanical): Divide motor into rotor and stator
2025-05-31 Feat(mechanical): Screw M1.6 T5 5mm countersink
2025-05-31 Feat(mechanical): Rotor adapter
2025-05-31 Feat(mechanical): Update motor and rotor adapter in assembly
2025-05-31 Feat(mechanical): Add rotor adapter heat-set insert
2025-05-31 Feat(mechanical): Test heat-set insert hole
2025-05-31 Refactor(mechanical): Rotor adapter heat-set insert chamfer
2025-05-31 Feat(mechanical): Chassis motor enclosure
2025-05-31 Feat(mechanical): Screw pan head M1.6 8mm
2025-05-31 Feat(mechanical): Chassis top enclosure
2025-05-31 Feat: Attach MCU PCB to motor
2025-06-02 Feat(pcb): Create net classes in power PCB
2025-06-02 Feat(pcb): Route differential pairs in Power PCB
2025-06-03 Feat(pcb): Fix DRC for Power PCB
2025-06-03 Feat(pcb): Add power management sheet
2025-06-03 Docs: Initial README
2025-06-27 Fix(pcb): Add missing USB CC1 pull-down
2025-06-27 Refactor(pcb): Rename VIN to 5V in MCU PCB
2025-06-29 Feat(schematic): Automatic power source selection
2025-06-30 Feat(schematic): Update volt sense to use BAT54S
2025-07-02 Feat(schematic): Use STM32 ADCs for phases curr/volt
2025-07-04 Feat(schematic): Replace current sense resistors
2025-07-04 Feat(schematic): Replace INA239 with INA240
2025-07-05 Feat(schematic): High frequency voltage sense
2025-07-05 Fix(schematic): Power board ERC errors
2025-07-13 Feat(pcb): Route phase voltage sense
2025-07-13 Feat(pcb): Route power management
2025-07-13 Feat(pcb): Route motor phases
2025-07-14 Feat(pcb): Route volt/curr sense
2025-07-14 Fix(pcb): DRC errors
2025-07-14 Refactor(pcb): Update footprints
2025-07-14 Feat(pcb): Replace USB with Molex USB
2025-07-15 Refactor(schematic): Rename INA nets to CURR
2025-07-15 Feat(pcb): Route current sense
2025-07-15 Feat(pcb): Initial MCU PCB routing
2025-07-15 Fix(pcb): MCU PCB DRC errors
2025-07-18 Feat: v1.0 MCU/Power PCBs ready
2025-07-19 Feat: PCB adjustments for manufacturing
2025-07-19 Feat: Add schematic PDFs for v1.0 PCBs
2025-07-20 Feat: Populate PCB page footer
2025-07-20 Docs: README table of contents
2025-07-20 Docs: Update PCB images and info
2025-07-20 Refactor(pcb): Update stackup colors
2025-07-20 Feat: Add brenocq-kicad-library as git submodule
2025-07-20 Feat: Setup KiCad project specific libraries
2025-07-20 Fix: PCB 3D model references
2025-07-20 Docs: Update library installation instructions
2025-07-20 Docs: Links to v1.0 PCBs release files
2025-08-16 Feat(fw): Add FreeRTOS source files
2025-08-16 Feat(fw): PCB v1.0 heartbeat
2025-08-16 Feat(fw): Handle multiple flags in build script
2025-08-16 Feat(fw): Update pinout to v1.0
2025-08-30 Fix(fw): UART DMA transmission
2025-08-30 Refactor(fw): Simplify DMA get methods
2025-08-30 Feat(fw): Use circular buffer in UART
2025-08-30 Refactor(fw): UART receive logic
2025-08-31 Feat(fw): Compile & link FreeRTOS
2025-08-31 Feat(fw): FreeRTOS running tasks
2025-08-31 Refactor(fw): Simplify main
2025-08-31 Refactor(fw): Move task creation to separate file
2025-08-31 Feat(fw): Voltage driver for src/u/v/w
2025-08-31 Feat(fw): Current driver for u/v/w
2025-09-01 Feat(fw): Add prescaler and datasize options to SPI config
2025-09-01 Fix(fw): IMU initialization
2025-09-01 Feat(fw): Read IMU temperature
2025-09-10 Feat(fw): Read encoder angle/magnitude
2025-09-11 Style(schematic): Add USART6 to text box
2025-09-11 Refactor(mechanical): Remove center of mass from screw
2025-09-11 Feat(fw): Validated phase voltage control with PWM
